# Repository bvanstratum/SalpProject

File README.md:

# SalpProject
Bio-inspired pulsed jet Swimmers

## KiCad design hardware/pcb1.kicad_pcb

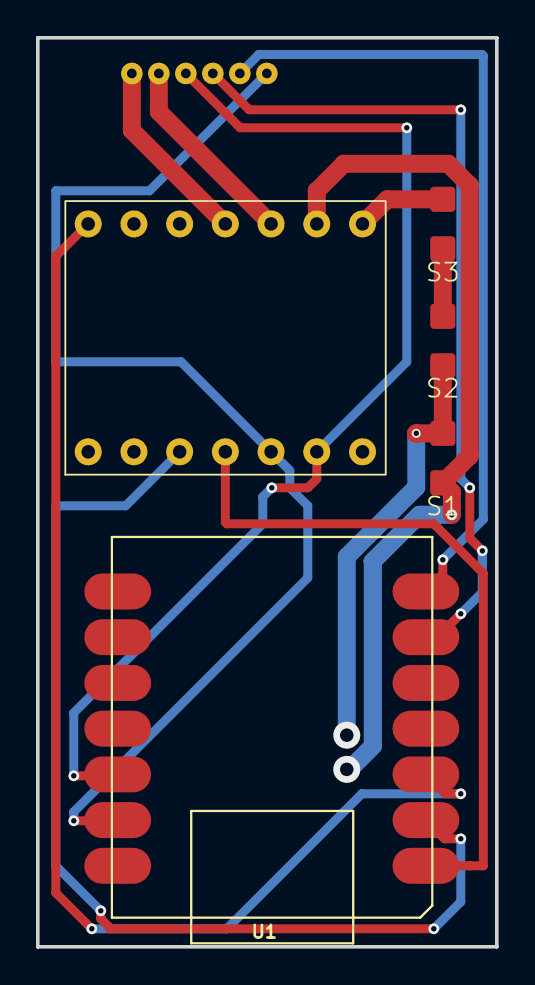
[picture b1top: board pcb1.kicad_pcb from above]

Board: 2 copper layers, 25.5 x 50.5 mm, 6 parts (0 on the bottom side), 13 nets.

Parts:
J1: Conn_01x06_MountingPin; JST_SH_6-pin connector
S1, S2, S3: Battery_Cell; battery pads
U1: MOUDLE-SEEEDUINO-XIAO-ESP32S3; MOUDLE14P-SMD-2.54-21X17.8MM
U2: DRV8874 Single Brushed DC Motor Driver Carrier

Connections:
GND: S1.2 (-), U2.9 (GND)
unnamed: J1.1 (GND), U1.13 (GND), U2.5 (PMODE)
unnamed: J1.6 (M1), U2.11 (OUT2)
unnamed: J1.5 (M2), U2.10 (OUT1)
unnamed: J1.3 (OUT_A), U1.6 (PA9_A5_D5_SCL)
unnamed: J1.2 (OUT_B), U1.7 (PB08_A6_TX)
unnamed: J1.4 (VCC), U1.12 (3V3), U2.6 (SLEEP)
unnamed: S1.1 (+), S2.2 (-)
unnamed: S2.1 (+), S3.2 (-)
unnamed: S3.1 (+), U2.8 (VIN)
unnamed: U1.1 (PA02_A0_D0), U2.4 (PH/IN2)
unnamed: U1.2 (PA4_A1_D1), U2.3 (EN/IN1)
unnamed: U1.3 (PA10_A2_D2), U2.14 (CS)

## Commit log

2026-02-20 Create README.md
    initial creation
2026-02-20 add prject structure and initial files
2026-02-20 Add .gitignore for KiCAD and Arduino
2026-02-20 added meeting notes
2026-02-20 organized and added more Markdown stuff
2026-02-20 Updated notes
2026-03-04 Add files via upload
    I have the zip file with the gerber and drill files. I also have have the KICAD schematic and board layouts.
2026-03-04 updated gbr files
2026-03-04 updated board layout with non-tented vias
2026-03-10 fattened some traces connected to motor controller
